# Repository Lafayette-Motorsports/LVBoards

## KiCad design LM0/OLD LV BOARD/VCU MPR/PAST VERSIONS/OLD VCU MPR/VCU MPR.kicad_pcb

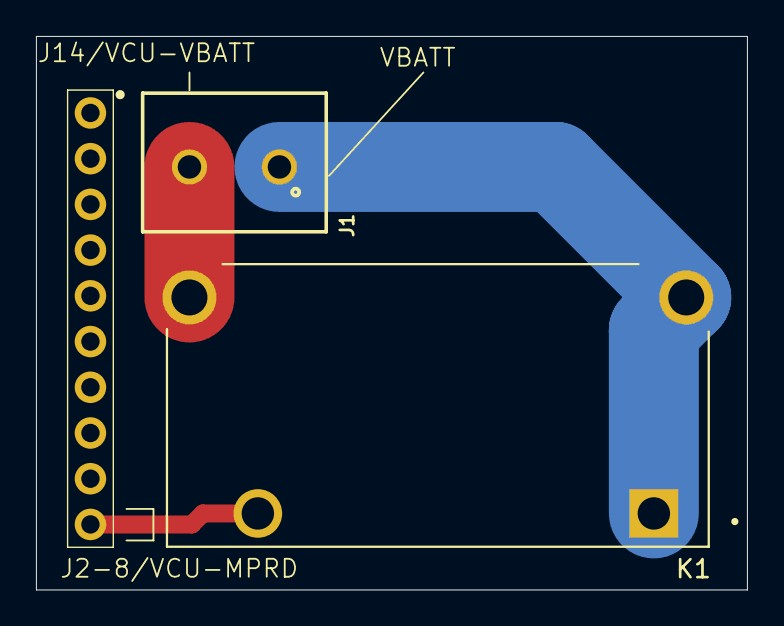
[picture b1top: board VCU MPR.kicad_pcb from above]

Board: 2 copper layers, 39.5 x 30.8 mm, 3 parts (0 on the bottom side), 3 nets.

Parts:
J1: 691137710002
J2: PH1-10-UA; 1X10-2.54MM-THT
K1: ALF1PF12; RELAY_ALF1PF12

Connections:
/VBATT: J1.1, K1.1, K1.3
/VCU VBATT: J1.2, K1.4
VCU-MPRD: J2.10, K1.2

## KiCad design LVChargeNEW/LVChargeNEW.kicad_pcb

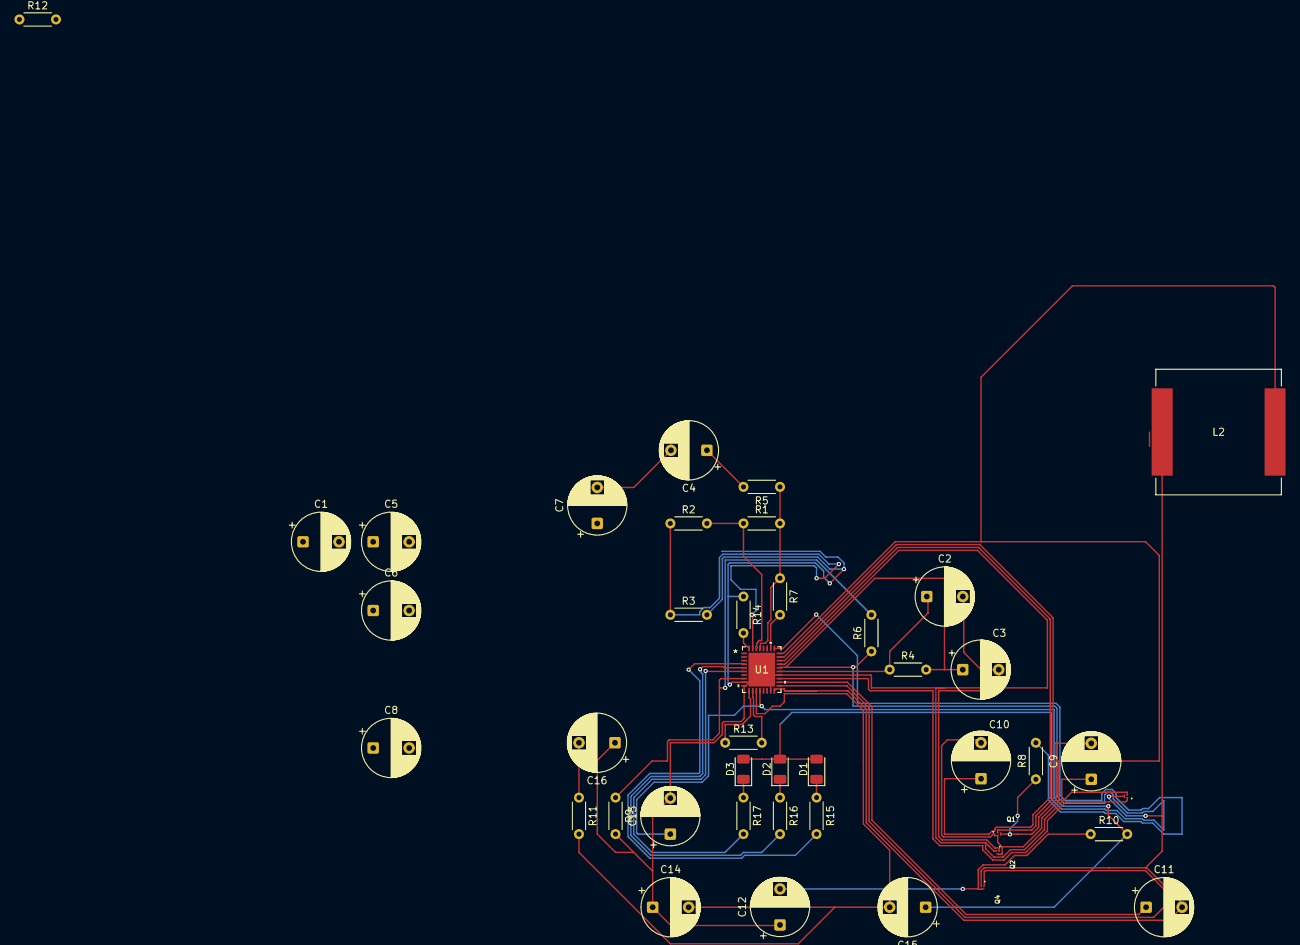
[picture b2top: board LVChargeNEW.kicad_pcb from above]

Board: 2 copper layers, 42 parts (0 on the bottom side), 32 nets.

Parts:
C1: 1uF; CP_Radial_D8.0mm_P5.00mm
C2, C3: 4.7uF; CP_Radial_D8.0mm_P5.00mm
C4, C6, C7: 100uF; CP_Radial_D8.0mm_P5.00mm
C5, C9, C12, C16: 80uF; CP_Radial_D8.0mm_P5.00mm
C8, C15: 470nF; CP_Radial_D8.0mm_P5.00mm
C10, C11, C13, C14: 100nF; CP_Radial_D8.0mm_P5.00mm
D1, D2, D3: LED; LED_1206_3216Metric
L2: SRP1770TA-150M; SRP1770TA_150M
Q1, Q2, Q3, Q4: CSD15380F3T; CSD15380F3
R1, R4: 100k; R_Axial_DIN0204_L3.6mm_D1.6mm_P5.08mm_Horizontal
R2: 53.8k; R_Axial_DIN0204_L3.6mm_D1.6mm_P5.08mm_Horizontal
R3: 85.4k; R_Axial_DIN0204_L3.6mm_D1.6mm_P5.08mm_Horizontal
R5: 2.4; R_Axial_DIN0204_L3.6mm_D1.6mm_P5.08mm_Horizontal
R6: 5.24k; R_Axial_DIN0204_L3.6mm_D1.6mm_P5.08mm_Horizontal
R7, R8, R10, R11: 10; R_Axial_DIN0204_L3.6mm_D1.6mm_P5.08mm_Horizontal
R9: 30.31k; R_Axial_DIN0204_L3.6mm_D1.6mm_P5.08mm_Horizontal
R12, R13: 249k; R_Axial_DIN0204_L3.6mm_D1.6mm_P5.08mm_Horizontal
R14: 133k; R_Axial_DIN0204_L3.6mm_D1.6mm_P5.08mm_Horizontal
R15, R16, R17: 10k; R_Axial_DIN0204_L3.6mm_D1.6mm_P5.08mm_Horizontal
U1: PQ25856QWRRVRQ1; Q25856QWRRVRQ1

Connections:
Batt3: R6.2, R9.1, U1.8 (TS)
Batt+: C16.2, R11.1, R12.2
Batt-: C1.1, C2.2, C3.2, C4.2, C5.2, C6.1, C7.2, C9.1, C12.1, C13.2, C14.1, C16.1, Q2.2, Q3.2, R3.2, R9.2, R14.1, U1.9 (ICHG), U1.10 (ILIM_HIZ), U1.17 (PGND), U1.22 (PGND), U1.37 (EPAD)
Buck Input: C1.2, C5.1, R1.2, R5.1, R7.1, U1.33 (VAC)
unnamed: C4.1, R5.2
unnamed: C9.2, Q1.3, R8.1
unnamed: C12.2, Q4.3, R10.1
unnamed: C3.1, D1.2 (A), D2.2 (A), D3.2 (A), R4.2, R6.1, U1.24 (REGN)
unnamed: D1.1 (K), R15.1
unnamed: D2.1 (K), R16.1
unnamed: D3.1 (K), R17.1
unnamed: R17.2, U1.6 (*PG)
unnamed: C7.1, C8.1, R8.2, U1.29 (ACN)
unnamed: R2.1, R3.1, U1.35 (ACOV)
unnamed: C6.2, C8.2, R7.2, U1.30 (ACP)
unnamed: R1.1, R2.2, U1.34 (ACUV)
unnamed: C10.1, U1.26 (BTST1)
unnamed: C11.1, U1.20 (BTST2)
unnamed: C2.1, R4.1, U1.23 (DRV_SUP)
unnamed: R12.1, R13.2, U1.12 (FB)
unnamed: R13.1, U1.11 (FBG)
unnamed: R14.2, U1.36 (FSW_SYNC)
unnamed: Q1.1, U1.27 (HIDRV1)
unnamed: Q4.1, U1.19 (HIDRV2)
unnamed: Q2.1, U1.25 (LODRV1)
unnamed: Q3.1, U1.21 (LODRV2)
unnamed: C14.2, C15.2, R11.2, U1.13 (SRN)
unnamed: C13.1, C15.1, R10.2, U1.14 (SRP)
unnamed: R15.2, U1.4 (STAT1)
unnamed: R16.2, U1.5 (STAT2)
unnamed: C10.2, L2.2, Q1.2, Q2.3, U1.28 (SW1)
unnamed: C11.2, L2.1, Q3.3, Q4.2, U1.18 (SW2)

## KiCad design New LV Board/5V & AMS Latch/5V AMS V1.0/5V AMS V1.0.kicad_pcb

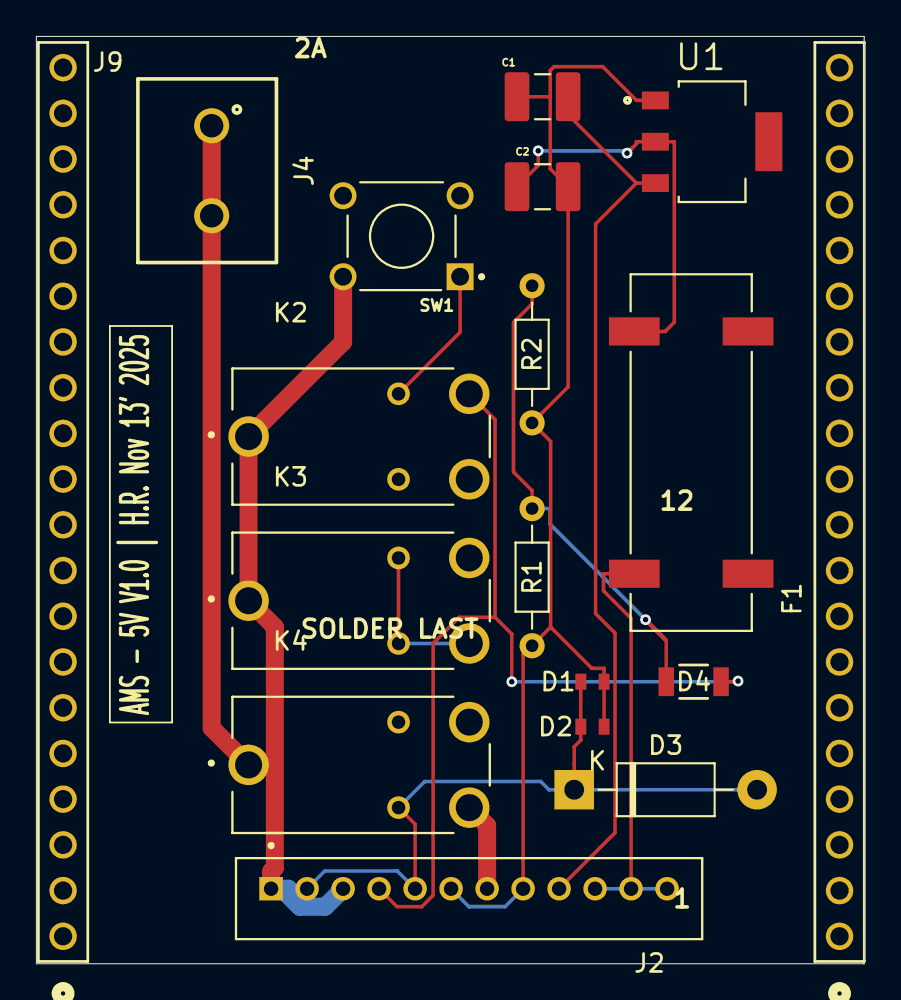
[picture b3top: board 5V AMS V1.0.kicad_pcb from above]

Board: 2 copper layers, 46.0 x 51.5 mm, 18 parts (0 on the bottom side), 12 nets.

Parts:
C1: 10u; CAPC3225X270N
C2: 47u; CAPC3225X270N
D1, D2: D_Zener; STA_RMCF0603_STP-L
D3: 1N4001; D_DO-41_SOD81_P10.16mm_Horizontal
D4: LED (Test); LED_AP3216SYD_KNB
F1: 3587TR; FUSE_3587
J2: B12B-PH-K-S; JST_B12B-PH-K-S
J4: 691137710002
J6, J9: PH1-20-UA; CONN_PH1-20-UA_ADM
K2, K3, K4: A161CS12VDC.64; RELAY_A161CS12VDC.64
R1, R2: 1k; R_Axial_DIN0204_L3.6mm_D1.6mm_P7.62mm_Horizontal
SW1: Test Reset AMS; psuhButton
U1: LT1117-5.0; REG_LT1117CST-5_TRPBF

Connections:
/GND: C1.2, C2.2, D1.2 (A), D2.2 (A), J2.6, J2.8, R1.1, R2.1, U1.1 (GND)
/Vs: C1.1, J2.9, U1.3 (VI)
unnamed: D1.1 (K), K4.A2
unnamed: D2.1 (K), D3.1 (K), J2.2, K2.A2, K3.A2, K3.NO, K4.A1, SW1.1
unnamed: D3.2 (A), J2.5, K2.A1, K3.A1
unnamed: D4.2 (A), J2.4, K2.NC
unnamed: D4.1 (K), R1.2, R2.2
unnamed: F1.1_1, J2.10, J2.11, J2.12
unnamed: J2.1, J2.3, K2.COM, K3.COM, SW1.2
unnamed: J2.7, K4.NO
unnamed: J4.1, J4.2, K4.COM
unnamed: C2.1, F1.2_1, U1.2 (VO)

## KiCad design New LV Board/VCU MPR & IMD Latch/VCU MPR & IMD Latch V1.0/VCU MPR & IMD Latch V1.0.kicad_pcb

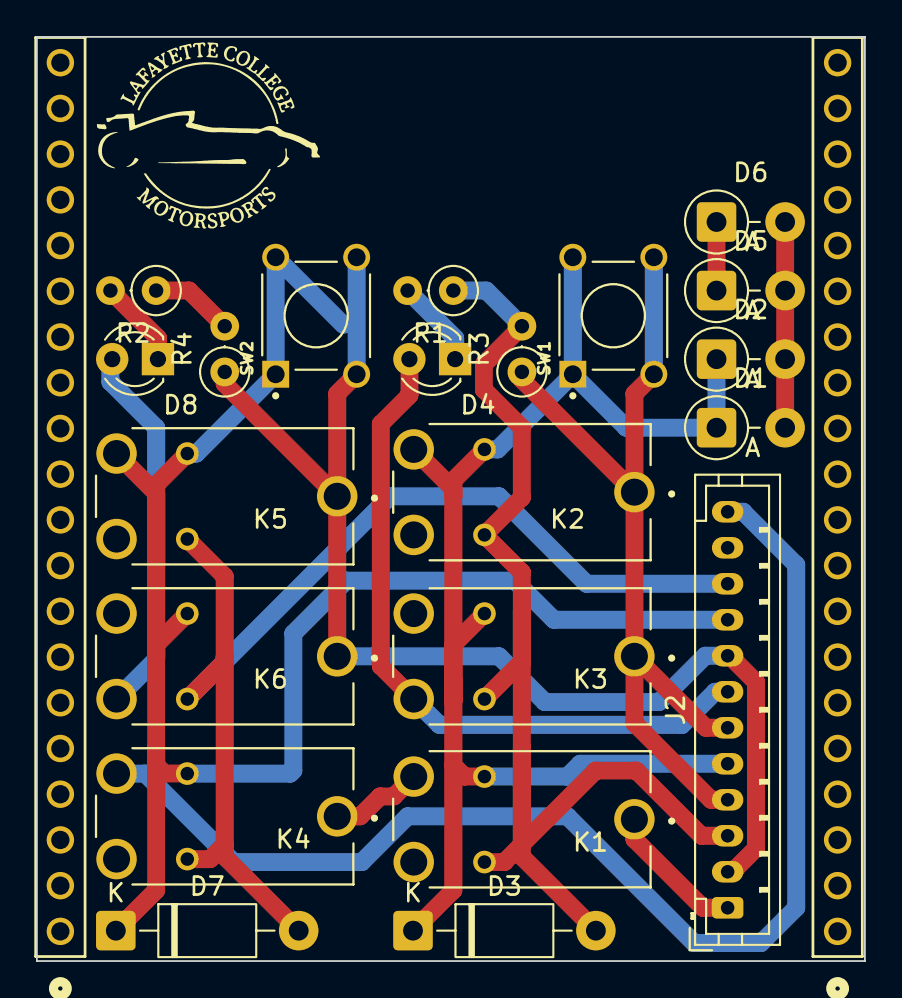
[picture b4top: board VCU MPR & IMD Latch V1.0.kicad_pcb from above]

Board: 2 copper layers, 46.0 x 51.3 mm, 23 parts (0 on the bottom side), 13 nets.

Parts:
D1, D2, D5, D6: 1N4743A; D_DO-41_SOD81_P3.81mm_Vertical_AnodeUp
D3, D7: 1N4001; D_DO-41_SOD81_P10.16mm_Horizontal
D4, D8: LED (Test); LED_D3.0mm
J2: B12B-PH-K-S; JST_PH_B12B-PH-K_1x12_P2.00mm_Vertical
K1, K2, K3, K4, K5, K6: A161CS12VDC.64; RELAY_A161CS12VDC.64
P1, P2: PH1-20-UA; CONN_PH1-20-UA_ADM
R1, R2: 680; R_Axial_DIN0207_L6.3mm_D2.5mm_P2.54mm_Vertical
R3, R4: 2.2k; R_Axial_DIN0207_L6.3mm_D2.5mm_P2.54mm_Vertical
SW1, SW2: Test Reset IMD; pushButton

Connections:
unnamed: D1.2 (A), D2.2 (A), D3.2 (A), D5.2 (A), D6.2 (A), J2.3, K1.A1, K2.A1, K3.A1, R1.1, R2.1, R3.2, R4.2
unnamed: D1.1 (K), D2.1 (K), D3.1 (K), J2.5, K1.A2, K2.A2, K2.NO, K3.A2, SW1.1
unnamed: D4.2 (A), J2.7, K3.NC
unnamed: D4.1 (K), R1.2
unnamed: D5.1 (K), D6.1 (K), D7.1 (K), J2.9, K4.A2, K5.A2, K5.NO, K6.A2, SW2.1
unnamed: D7.2 (A), J2.10, K4.A1, K5.A1, K6.A1
unnamed: D8.2 (A), J2.11, K6.NC
unnamed: D8.1 (K), R2.2
unnamed: J2.1, K1.COM
unnamed: J2.2, J2.8, K5.COM, K6.COM, R4.1, SW2.2
unnamed: J2.4, J2.6, K2.COM, K3.COM, R3.1, SW1.2
unnamed: J2.12, K4.NO
unnamed: K1.NO, K4.COM

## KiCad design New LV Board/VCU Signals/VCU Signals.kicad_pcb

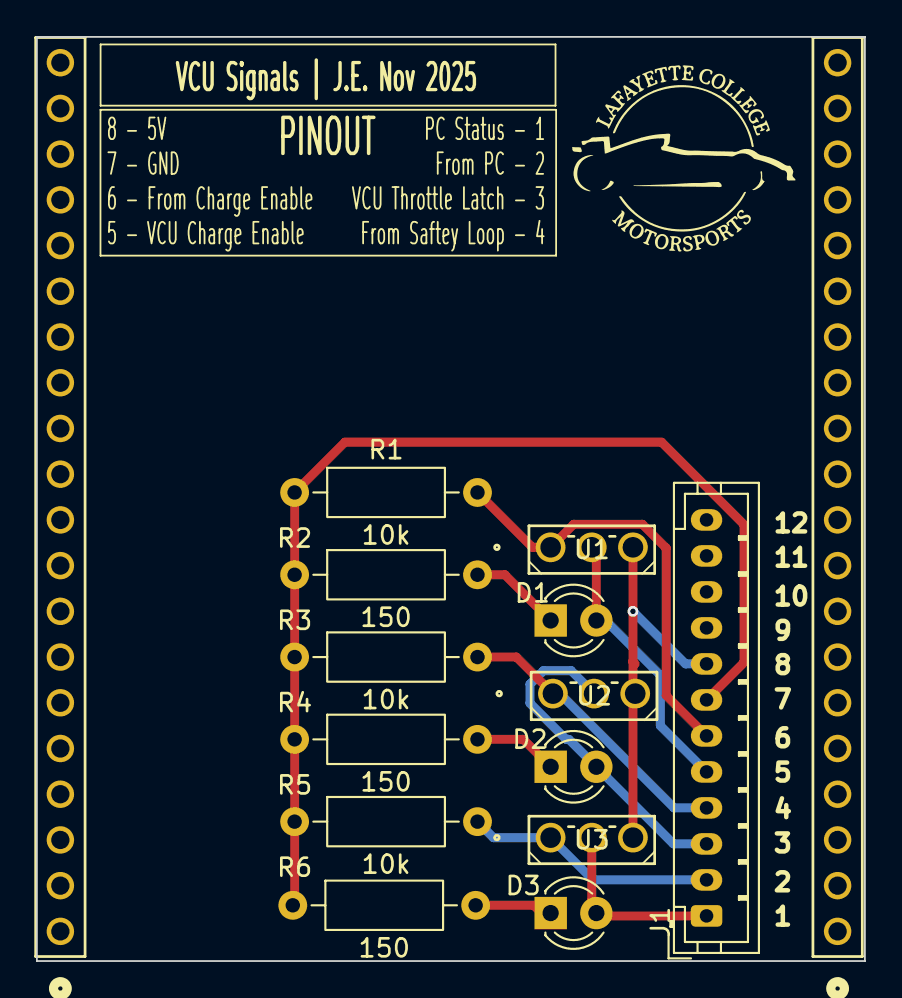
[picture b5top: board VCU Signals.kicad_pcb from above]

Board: 2 copper layers, 46.0 x 51.3 mm, 15 parts (0 on the bottom side), 11 nets.

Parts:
D1, D2, D3: LED (Test); LED_D3.0mm
J1: B12B-PH-K-S:JST_B12B-PH-K-S; JST_PH_B12B-PH-K_1x12_P2.00mm_Vertical
P1, P2: PH1-20-UA; CONN_PH1-20-UA_ADM
R1, R3, R5: 10k; R_Axial_DIN0207_L6.3mm_D2.5mm_P10.16mm_Horizontal
R2, R4, R6: 150; R_Axial_DIN0207_L6.3mm_D2.5mm_P10.16mm_Horizontal
U1, U2, U3: IRLML2060TRPBF; DPAK-3_6P35X6P73_ONS

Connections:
unnamed: D1.2 (A), J1.5, U1.2 (S)
unnamed: D1.1 (K), R2.2
unnamed: D2.2 (A), J1.3, U2.2 (S)
unnamed: D2.1 (K), R4.2
unnamed: D3.2 (A), J1.1, U3.2 (S)
unnamed: D3.1 (K), R6.2
unnamed: J1.7, R1.1, R2.1, R3.1, R4.1, R5.1, R6.1
unnamed: J1.8, U1.3 (D), U2.3 (D), U3.3 (D)
unnamed: J1.6, R1.2, U1.1 (G)
unnamed: J1.4, R3.2, U2.1 (G)
unnamed: J1.2, R5.2, U3.1 (G)

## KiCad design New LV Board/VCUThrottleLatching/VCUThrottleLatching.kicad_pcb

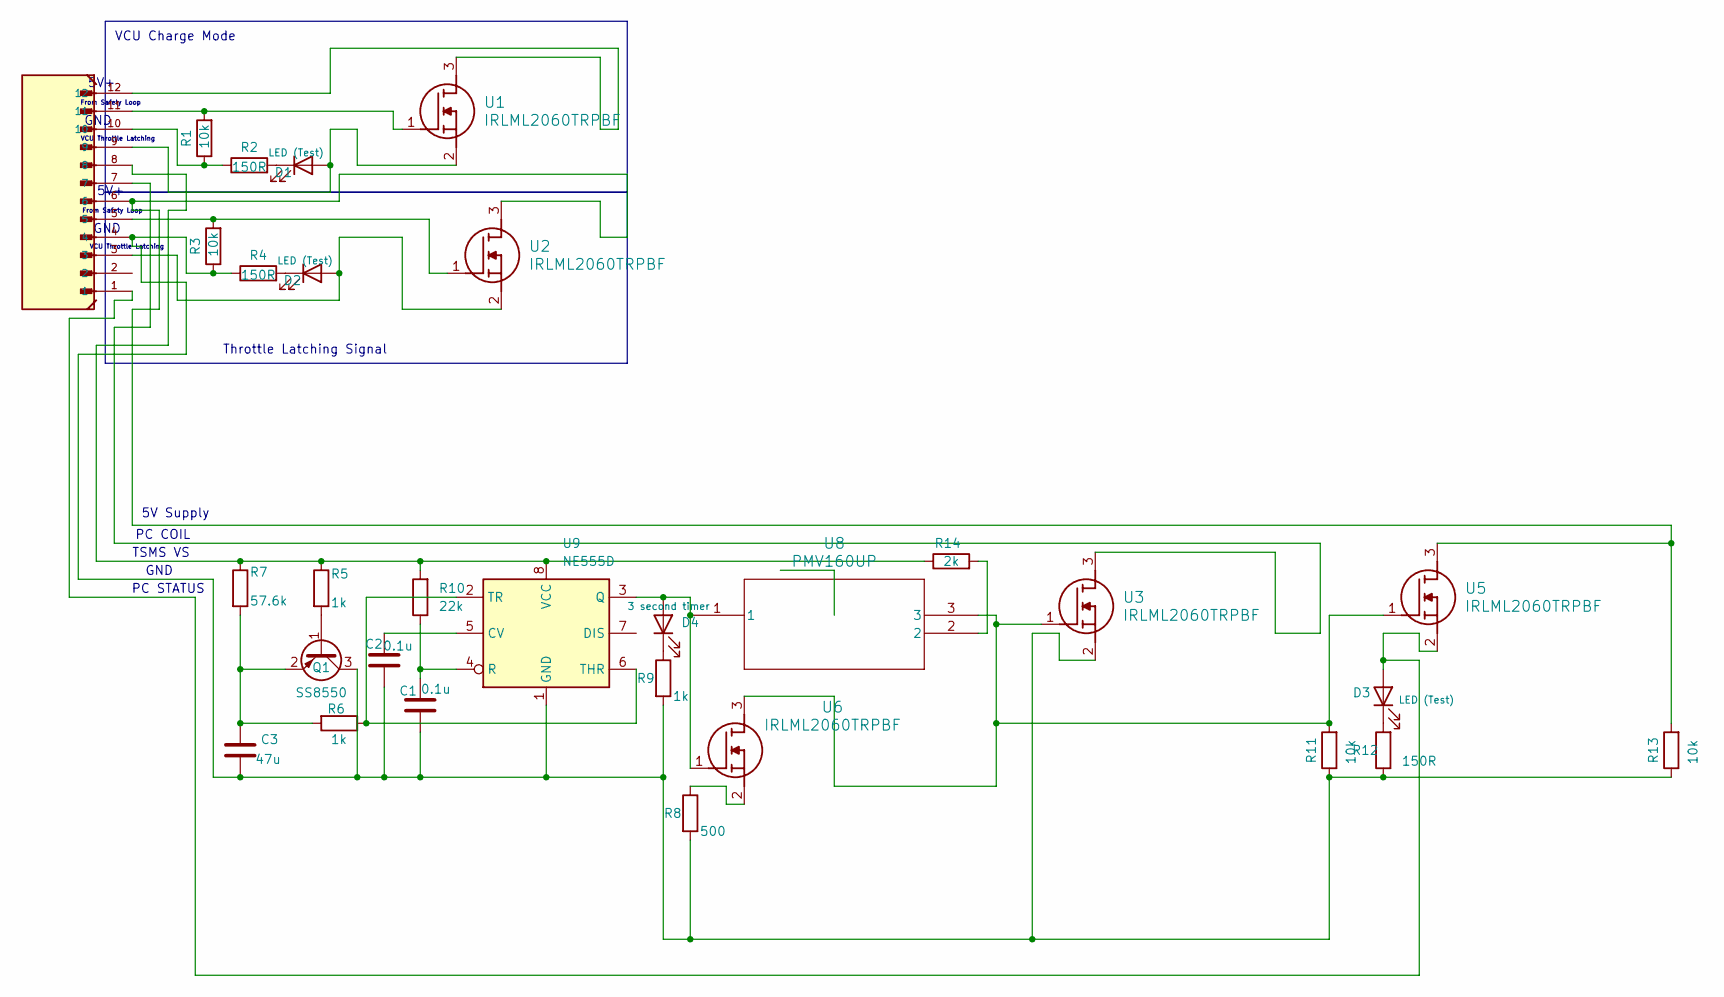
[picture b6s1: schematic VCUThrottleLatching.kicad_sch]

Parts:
C1, C2: 0.1u; C_0201_0603Metric
C3: 47u; C_0201_0603Metric
D1, D2, D3: LED (Test); LED_D3.0mm
D4: 3 second timer; LED_D3.0mm
J1: B12B-PH-K-S:JST_B12B-PH-K-S; PinHeader_1x12_P2.54mm_Vertical
Q1: SS8550; SOT95P237X112-3N
R1, R3, R11, R13: 10k; STA_CF14_STP
R2, R4, R12: 150R; STA_CF14_STP
R5, R6, R9: 1k; STA_CF14_STP
R7: 57.6k; STA_CF14_STP
R8: 500; STA_CF14_STP
R10: 22k; STA_CF14_STP
R14: 2k; STA_CF14_STP
U1, U2, U3, U5, U6: IRLML2060TRPBF; SOT95P237X112-3N; Manufacturer_Part_Number IRLML2060TRPBF; Mouser Part Number 942-IRLML2060TRPBF
U8: PMV160UP; SOIC127P599X175-8N
U9: NE555D; SOIC127P599X175-8N

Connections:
unnamed: D1.2 (A), J1.9, U1.2 (S)
unnamed: D1.1 (K), R2.2
unnamed: D2.2 (A), J1.3, U2.2 (S)
unnamed: D2.1 (K), R4.2
unnamed: D3.2 (A), J1.1, U5.2 (S)
unnamed: D3.1 (K), R12.2
unnamed: D4.2 (A), U6.1 (G), U8.1, U9.3 (Q)
unnamed: D4.1 (K), R9.1
unnamed: J1.10, R1.1, R2.1
unnamed: Q1.1 (B), R5.2
unnamed: C1.2, C2.2, C3.2, J1.4, Q1.3 (C), R3.1, R4.1, R8.2, R9.2, R11.1, R12.1, R13.1, U3.2 (S), U9.1 (GND)
unnamed: C3.1, Q1.2 (E), R6.2, R7.2
unnamed: R14.2, U8.2
unnamed: J1.12, U1.3 (D)
unnamed: J1.11, R1.2, U1.1 (G)
unnamed: J1.6, R13.2, U2.3 (D), U5.3 (D)
unnamed: J1.5, R3.2, U2.1 (G)
unnamed: J1.7, U3.3 (D)
unnamed: R11.2, U3.1 (G), U5.1 (G), U6.3 (D), U8.3
unnamed: R8.1, U6.2 (S)
unnamed: C2.1, U9.5 (CV)
unnamed: C1.1, R10.1, U9.4 (R)
unnamed: R6.1, U9.2 (TR), U9.6 (THR)
unnamed: J1.8, R5.1, R7.1, R10.2, R14.1, U9.8 (VCC)

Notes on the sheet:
VCU Charge Mode
VCU Throttle Latching
5V Supply
GND
GND
Throttle Latching Signal
From Safety Loop
PC COIL
5V+
TSMS VS
PC STATUS

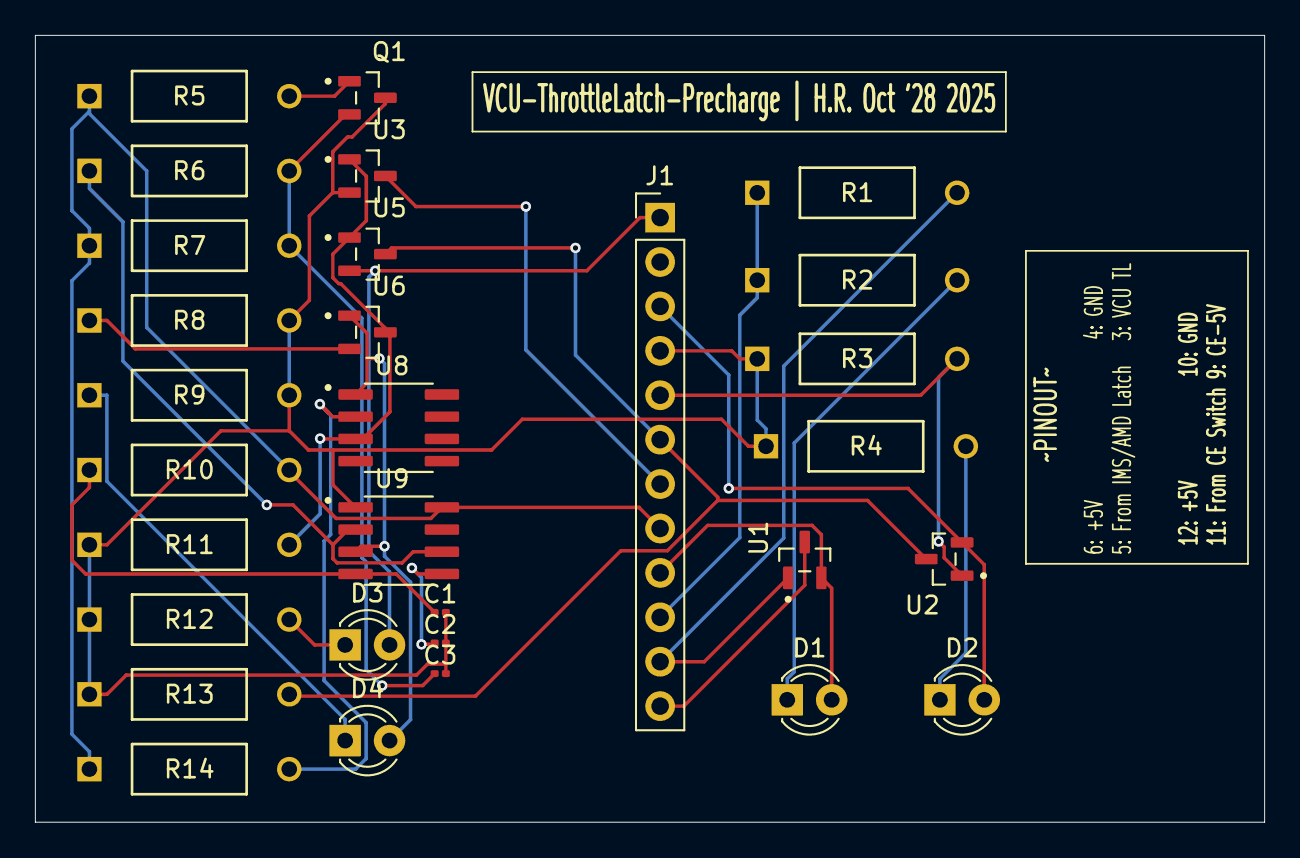
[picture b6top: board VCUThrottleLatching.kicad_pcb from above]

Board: 2 copper layers, 70.3 x 45.0 mm, 30 parts (0 on the bottom side), 24 nets.

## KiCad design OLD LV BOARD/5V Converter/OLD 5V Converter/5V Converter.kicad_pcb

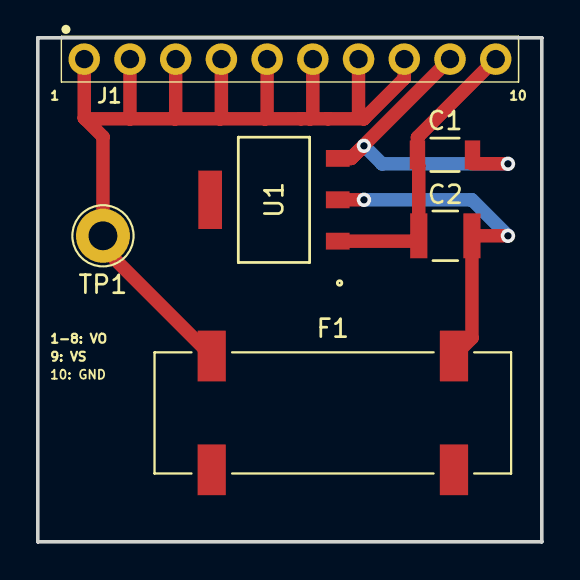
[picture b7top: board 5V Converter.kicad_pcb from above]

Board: 2 copper layers, 28.0 x 28.0 mm, 6 parts (0 on the bottom side), 4 nets.

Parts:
C1: 10u; CAP_CL31_SAM
C2: 47u; CAP_CL32_SAM
F1: 3587TR; FUSE_3587TR
J1: PH1-10-UA; 1X10-2.54MM-THT
TP1: TestPoint; TestPoint_Loop_D2.60mm_Drill1.6mm_Beaded
U1: LT1117-5.0; SOT-223_ST_LIT-M

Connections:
/GND: C1.2, C2.2, J1.10, U1.1 (GND)
/Vs: C1.1, J1.9, U1.3 (VI)
unnamed: F1.1_1, J1.1, J1.2, J1.3, J1.4, J1.5, J1.6, J1.7, J1.8, TP1.1
unnamed: C2.1, F1.2_1, U1.2 (VO)
